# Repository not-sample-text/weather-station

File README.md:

# Stație Meteo cu Arduino

## Descriere Proiect

Acest proiect reprezintă o stație meteo compactă bazată pe Arduino, care măsoară temperatura, presiunea atmosferică și altitudinea folosind senzorul BMP280. Datele sunt afișate pe un ecran TFT ILI9341 color, inclusiv grafice pentru istoricul valorilor măsurate.

Stația meteo este dezvoltată de Pal Antonio și Hausi Alexandru ca parte a unui proiect educațional pentru monitorizarea parametrilor atmosferici.

## Caracteristici

- Măsurarea în timp real a temperaturii (°C)
- Măsurarea presiunii atmosferice (hPa)
- Calcularea altitudinii bazată pe presiunea la nivelul mării
- Afișare grafică a istoricului temperaturii și presiunii
- Interfață vizuală intuitivă cu coduri de culori
- Actualizare automată a datelor la fiecare 2.5 secunde

## Schema Electronică

Acest proiect include o schemă electronică completă creată în KiCad, disponibilă în directorul `/schematics`. Schema detaliază toate conexiunile necesare între Arduino, senzorul BMP280 (conectat prin adaptorul de nivel logic TXS0108E) și ecranul TFT ILI9341.

## Structura Codului

Codul sursă este organizat în mai multe fișiere pentru o mai bună modularitate:

- **DisplayManager**: Gestionează afișajul TFT și toate elementele grafice
- **SensorManager**: Gestionează comunicarea cu senzorul BMP280 și procesarea datelor
- **main.ino**: Fișierul principal care coordonează toate componentele

## Dependențe

Acest proiect necesită următoarele biblioteci:

- [Adafruit GFX Library](https://github.com/adafruit/Adafruit-GFX-Library) (v1.11.5+)
- [Adafruit ILI9341 Library](https://github.com/adafruit/Adafruit_ILI9341) (v1.5.12+)
- [Adafruit BMP280 Library](https://github.com/adafruit/Adafruit_BMP280_Library) (v2.6.6+)
- [Adafruit Sensor Library](https://github.com/adafruit/Adafruit_Sensor) (v1.1.5+)
- Arduino Wire Library (inclusă în Arduino IDE)
- Arduino SPI Library (inclusă în Arduino IDE)

### Instalarea Bibliotecilor

1. Deschideți Arduino IDE
2. Mergeți la Sketch > Include Library > Manage Libraries...
3. Căutați și instalați fiecare dintre bibliotecile Adafruit menționate mai sus
4. Reporniți Arduino IDE
5. Deschideți proiectul și încărcați-l pe placa dvs. Arduino

## Componente Hardware Necesare

- Arduino (recomandat Arduino Uno/Nano/Mega)
- Senzor BMP280 de temperatură și presiune
- Ecran TFT ILI9341 (240x320 pixeli; Pentru acest proiect foloses unul de 2.4", SKU:MSP2401)
- Adaptor de nivel logic TXS0108E (pentru comunicarea cu senzorul BMP280)
- Cabluri de conexiune
- Sursă de alimentare corespunzătoare

## Instrucțiuni de Utilizare

1. Conectați toate componentele conform schemei KiCad din directorul `/schematics`
2. Instalați toate bibliotecile necesare
3. Încărcați codul pe placa Arduino
4. Stația meteo va începe să afișeze date imediat după pornire

## Contribuții

Contribuțiile sunt binevenite! Vă rugăm să citiți ghidul de contribuție pentru mai multe detalii.

## Licență

Acest proiect este distribuit sub licența MIT. Consultați fișierul `LICENSE` pentru detalii complete.

## Contact

Pentru întrebări sau sugestii, vă rugăm să deschideți un issue în acest repository sau să contactați autorii:

- Pal Antonio
- Hausi Alexandru

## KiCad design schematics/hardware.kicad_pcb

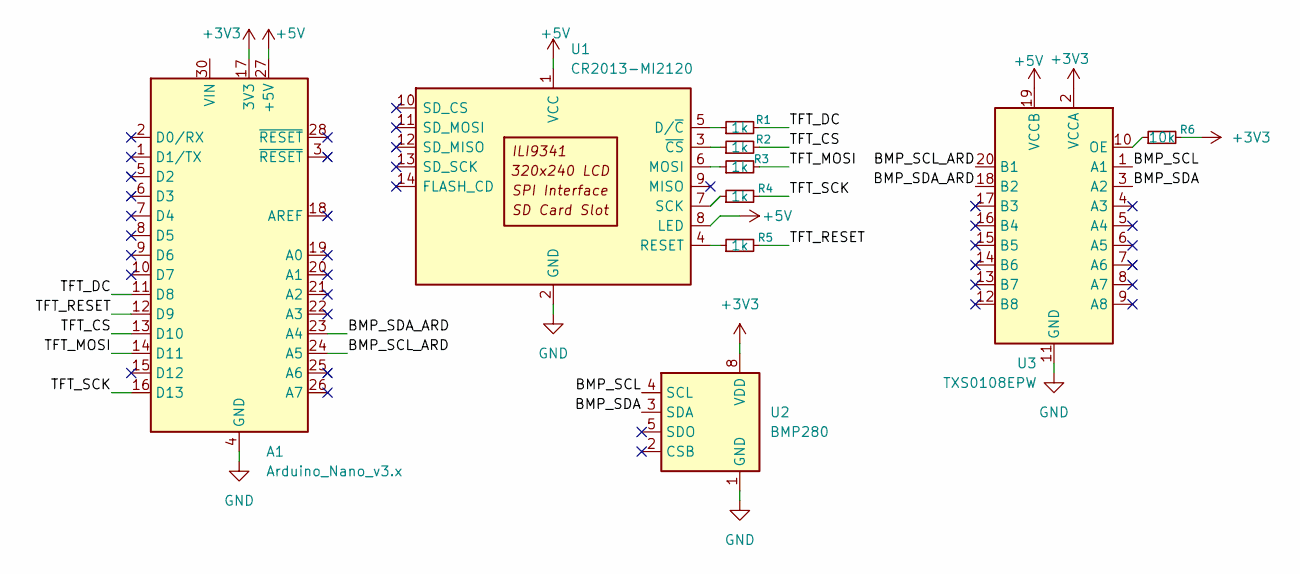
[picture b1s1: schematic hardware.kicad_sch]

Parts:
A1: Arduino_Nano_v3.x; Arduino_Nano
R1, R2, R3, R4, R5: 1k; R_Axial_DIN0207_L6.3mm_D2.5mm_P10.16mm_Horizontal
R6: 10k; R_Axial_DIN0207_L6.3mm_D2.5mm_P10.16mm_Horizontal
U1: CR2013-MI2120
U2: BMP280; Bosch_LGA-8_2x2.5mm_P0.65mm_ClockwisePinNumbering
U3: TXS0108EPW; TSSOP-20_4.4x6.5mm_P0.65mm

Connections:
+3V3: A1.17 (3V3), R6.2, U2.6 (VDDIO), U2.8 (VDD), U3.2 (VCCA)
+5V: A1.27 (+5V), U1.1 (VCC), U1.8 (LED), U3.19 (VCCB)
/BMP_SCL: U2.4 (SCL), U3.1 (A1)
/BMP_SCL_ARD: A1.24 (A5), U3.20 (B1)
/BMP_SDA: U2.3 (SDA), U3.3 (A2)
/BMP_SDA_ARD: A1.23 (A4), U3.18 (B2)
/TFT_CS: A1.13 (D10), R2.2
/TFT_DC: A1.11 (D8), R1.2
/TFT_MOSI: A1.14 (D11), R3.2
/TFT_RESET: A1.12 (D9), R5.2
/TFT_SCK: A1.16 (D13), R4.2
GND: A1.4 (GND), A1.29 (GND), U1.2 (GND), U2.1 (GND), U2.7 (GND), U3.11 (GND)
unnamed: R1.1, U1.5 (D/~C)
unnamed: R3.1, U1.6 (MOSI)
unnamed: R5.1, U1.4 (RESET)
unnamed: R4.1, U1.7 (SCK)
unnamed: R2.1, U1.3 (~CS)
unnamed: R6.1, U3.10 (OE)

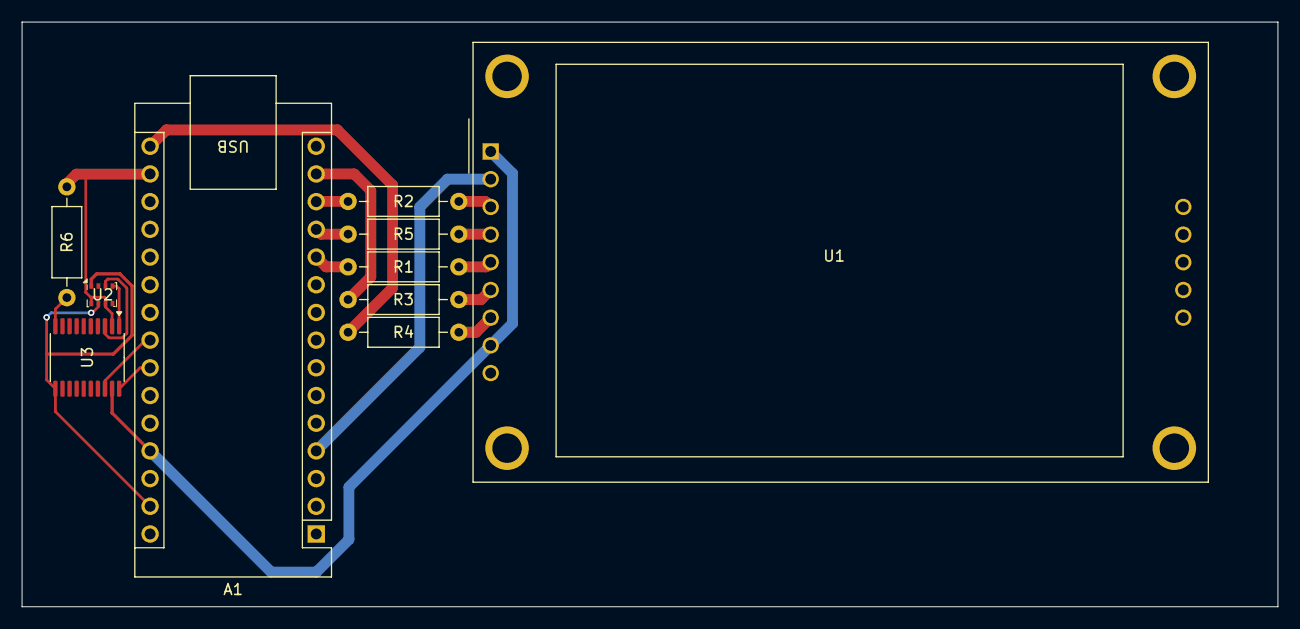
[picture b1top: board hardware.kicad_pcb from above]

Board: 2 copper layers, 115.2 x 53.6 mm, 10 parts (0 on the bottom side), 18 nets.

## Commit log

2025-05-08 update basically everything
2025-05-09 updated hardware - wiring tbd added gitignore for kicad backups
2025-05-09 finished schematic, pcbnew tbd
2025-05-09 Refactor DisplayManager to use PROGMEM for string storage and add overload for F() strings in drawError method
2025-05-09 pcbnew done
